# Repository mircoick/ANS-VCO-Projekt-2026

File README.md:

17.07.2026

<div align="center">

# VCO Design und Simulation

**Entwicklung und Inbetriebnahme eines Wien-Robinson-Oszillators als
Voltage-Controlled-Ozillator ($f_0=5,5~\text{MHz}$)**

<table style="border: none; border-collapse: collapse; margin: 0 auto;" border="0">

<tr style="border: none;">

<td style="border: none; padding: 0 25px; text-align: center;">

Tassilo Hertling

</td>

<td style="border: none; padding: 0 25px; text-align: center;">

Torben Becker

</td>

<td style="border: none; padding: 0 25px; text-align: center;">

Mirco Ick

</td>

</tr>

</table>

</br> </br>

**Dateiübersicht**

[KiCad-Dateien](kicad/) · [Simulationsdaten](sim/) · [Python
Code](code/) · [Datenblätter](datasheets/)

</div>

------------------------------------------------------------------------

# Einleitung

In diesem Projekt gilt es einen VCO (Voltage Controlled Oszillator) zu
designen und in Betrieb zu nehmen. Das Design soll bestimmte
Anforderungen erfüllen, damit es in einem Laborversuch als FM-Modulator
genutzt werden kann. In der Vergangenheit wurde im Laborversuch eine VCO
Schaltung mit alten und abgekündigkten Komponenten verwendet. Diese
Schaltung soll nun mit neuen und verfügbaren Komponenten erneuert
werden.

Die VCO Schaltung soll eine FM-Modulation mit einem Trägersignal bei der
Frequenz $5,5~\text{MHz}$ durchführen und einen Modulationsbereich
zwischen $5~\text{MHz}$ und $6~\text{MHz}$ verwenden. Der
Einstellungsbereich soll mit $1~\text{V}$ pro $1~\text{MHz}$ eingestellt
werden. Somit kann das zu modulierende Signal einen Spannungsbereich von
$V_{pp} = 1~\text{V}$ haben. Die Ein- und Ausgangsimpedanz soll
$50~\Omega$ betragen.

Zudem soll die Schaltung aus Komponenten bestehen, die Studierenden im
4.Semester bereits kennen, damit die Schaltung im Rahmen des
Laborversuchs im Grunde verstanden werden kann. Aus dieser
Rahmenbedingung folgt die Auswahl der spezifischen VCO-Schaltung.

Die Platine soll zudem relativ groß ausgelegt werden und es sollen
möglichst bedrahtete Bauteile verwendet werden. In dem Laborversuch soll
ebenfalls die Kennlinie des FM-Modulators aufgenommen werden. Hierfür
ist ein integrierter einstellbarer Spannungsteiler vorgesehen, der über
einen Drehregler auf der Platine eingestellt werden soll.

Die Schaltung soll ebenfalls Stabil gegenüber Schwankungen in der
Versorgungsspannung und somit in der Ausgangsfrequenz ausgelegt sein.
Anschlüsse für die im Laborversuch verwendeten Geräte wie das
Oszilloskop und dem Spektrumanalysator sollen über SMA- oder
BNC-Anschlüsse geschehen.

# Technische Spezifikationen (Kundenanforderungen)

- **Mittenfrequenz ($f_0$):** $5,5~\text{MHz}$ (Zwischenfrequenz / ZF)
  bei einer Steuerspannung von $0~\text{V}$.

- **Linearer Modulationsbereich:** $\pm 0,5~\text{MHz}$ (Frequenzhub)
  bei einer Steuerspannung von $\pm 0,5~\text{V}$.

  - *Arbeitsbereich:* $5,0~\text{MHz}$ bis $6,0~\text{MHz}$ linear im
    Spannungsbereich von $-0,5~\text{V}$ bis $+0,5~\text{V}$.

- **Frequenzstabilität:** Es darf keine Frequenzverschiebung (Drift)
  durch thermische oder externe Einflüsse auftreten.

- **Systemimpedanz:** Ein- und Ausgangswiderstand müssen exakt
  $50~\Omega$ betragen.

- **Steckverbinder:** Ein- und Ausgänge sind als **SMA-** oder
  **BNC-Buchsen** auszuführen.

- **Schaltungsarchitektur:** Einfacher, leicht zu verstehender und
  nachvollziehbarer Aufbau (diskreter Bauelemente).

- **Spannungsversorgung:** Integrierte Stabilisierung und Filterung der
  Versorgungsspannung zur Rauschunterdrückung.

- **Manuelle Steuerung:** Integrierter Spannungsteiler mit einem
  analogen Drehknopf (Potentiometer) zur Frequenzeinstellung.

- **Platinedesign:** Relativ große, robuste und mechanisch
  unempfindliche Leiterplatte.

- **Bestückungstechnologie:** Ausschließlich **stehende, bedrahtete
  Bauteile** für optimale Zugänglichkeit (keine SMD-Bauteile).

# Designverlauf

## Grundlegender VCO

Zuerst wurde im Design angefangen ein passendes VCO-Modell nach den
Anforderungen auszusuchen. Als Modell haben wurde sich für den LC-VCO
entschieden. Dieser besteht im Grunde aus einer RLC-Schaltung und einer
kreuzgekoppelten Mosfet-Schaltung. Das Design ist somit gut für
Studierende aus dem 4. Semester zu verstehen und kann auch gut mit
bedrahteten Bauteilen aufgebaut werden. Die Grundschaltung ist in
<a href="#fig-circuit" class="quarto-xref">Abbildung 1</a> zu sehen:

<div id="fig-circuit">

Abbildung 1: VCO-Grundschaltung

</div>

In der Grundschaltung sind im oberen Bereich die beiden Induktivitäten
$L1$ und $L2$ in doppelter Ausführung zu sehen, da die
Versorgungsspannung mittig angeschlossen werden muss, um die Symmetrie
der Schaltung gewärleisten zu können. Weiter unten ist der einstellbare
Kondensator $C1$ zu sehen, dessen Wert die Schwingung der Schaltung
maßgeblich beeinflusst. Durch die Änderung des Kondensator ändert sich
auch die Frequenz $f_0$ der Schaltung. Somit kann duch eine gesteuerte
Änderung der Kapazität die Frequenz der Schwingung eingestellt werden.
Das ist das Grundprinzip des VCO´s und die Funktionsweise der
FM-Modulation. Der Widerstand $R1$ vervollständigt den RLC-Schwingkreis.
Die beiden kreugekoppelten Mosfets sind für die ständige Anregung der
Schwingung zuständig. Durch die ständige Änderung der gesamt Impedanz
des Schwingkreises ändert sich jeweils der Strom, der durch die Mosfets
am Gate Eingang anliegt. Diese Änderung bewirkt eine Rückgekoppelte
Schleife, durch welche schwingt das System dauerhaft. Nach
Implementierung dieser Schaltung in KiCad, NG- sowie LT-Spice konnte die
Funktionsweise sowie das Einstellen der Frequenz $f_0$ klarer gemacht
werden.

Im Verlauf der Entwicklung wurde sich entschieden verschiede VCO Ansätze
zu entwerfen und am Ende dem Kunden zu präsentieren. Unter den drei
Gruppen konnte sich neben dem Grund-VCO, welcher oben bereits erklärt
wurde, der Colpitts Oszillator oder der Wien-Robinson-Oszillator
ausgesucht werden. Da sich bereits im zweiten Semester ausgiebig mit der
Wien-Robinson Brücke auseinander gesetzt wurde haben wir uns für diesen
VCO entschieden, auf welchen in den nachfolgenden Kapiteln näher
eingegangen wird.

Eine Simulationsdatei ist dem Ordner
[VCO-Schwingkreis](kicad/Archiv/VCO-Schwingkreis/) zu entnehmen.

## Wien-Robinson-Oszillator

Um den Wien-Robinson-Oszillator besser verstehen zu können wurde sich
als erstes die Grundschaltung, die Wien-Robinson-Brücke, nochmals
angeschaut. Hierbei handelt es sich um eine frequenzabhängige
Wechselstrom-Messbrücke, die als sogenannte Nullbrücke konzipiert ist.
Das bedeutet, dass die Differenzspannung in der Brückendiagonale bei
einer spezifischen Resonanzfrequenz exakt
$\underset{\scriptscriptstyle\sim}{U} = 0~\text{V}$ beträgt. Ein
Schaltung ist der
<a href="#fig-wienrobbruecke" class="quarto-xref">Abbildung 2</a> zu
entnehmen.

<div id="fig-wienrobbruecke">

Abbildung 2: Wien-Robinson-Brücke
(<span class="nocase">de-academic.com</span> 2000-2026)

</div>

Wenn man nun an diese Brückendiagonale einen Operationsverstärker (OPV)
einbaut, erhält man einen aktiven Oszillator, der die
Frequenzselektivität der Brücke nutzt. Da der OPV die verschwindend
geringe Differenzspannung im Bereich der Resonanzfrequenz extrem hoch
verstärkt, reicht bereits das thermische Rauschen der Bauteile aus, um
das System resonant anzuregen. Somit erhält man einen sich selber
anwingenden Oszillator. Diese Wien-Robinson-Oszillator Schaltung ist
eine der meistgenutzen Schaltungen einer Wien-Robinson-Brücke und bietet
somit eine gute Grundlage des VCO’s. Für die ersten Tests mit dem
Wien-Robinson-Oszillator wurde die Seite des Elektroniktutors
herangezogen und versucht, die entsprechende Schaltung nachzustellen
(Mietke 2002-2026).

<div id="fig-wien">

Abbildung 3: Wien-Robinson-Oszillator Schaltung (Mietke 2002-2026)

</div>

Die in <a href="#fig-wien" class="quarto-xref">Abbildung 3</a> zu
sehende Schaltung zeigt wie bereits erörtert den in der
Brückendiagonalen eingebaute Operationsverstärker und eine zusätzliche
Amplitudenregulierung. Durch die starke Anregung der Schwingung des
OPV’s wurde hier noch eine Amplitudenregelung eingebaut, welche aus
einem Potentiometer und zwei entgegengeschalteten Varktordioden besteht.
Ohne diese Amplitudenregelung würde die Schwingung aufgrund der
unendlichen Verstärkung des OPV schnell bis an die Grenzen der
Versorgungsspannung anwachsen und begrenzen, was zu starken Verzerrungen
des Sinussignals führen würde. Die Regelung sorgt dafür, dass sich ein
stabiler, verzerrungsfreier Dauerschwingzustand einstellt.

Nachdem nun diese Schaltung erfolgreich in KiCAD, erst auf der
ursprünglichen Resonanzfrequenz $f_0=1592~\text{Hz}$ und anschließend
mit Änderung des OPV’s (LT7171) auf die gewünschten $5,5~\text{MHz}$,
umgesetzt wurde, konnte sich um den geforderten Frequenzhub von
$\Delta f=1~\text{MHz}$ bei einer Steuerspannungsänderung von
$U_{str}=\pm 0,5~\text{V}$ gemacht werden. Für den ersten Entwurf wurden
nun Varaktoren parallel zu den beiden Kondensatoren $C$ geschaltet.

Nach umsetzen dieser Schaltung haben sich jedoch zwei Probleme
kristallisiert. Zum einen kamen in den verschiedenen Simulationen (KiCAD
bzw. NG-Spice und LT-Spice) unterschiede Ergebnisse heraus, und zum
anderen war es nicht möglich die Kennlinie der Resonanzfrequenz $f_0$
über die Steuerspannung $U_{str}$ linear zu bekommen. Nach vielen
vergeblichen Versuchen wurde sich dann dazu entschieden den kompletten
Aufbau neu aufzusetzen und eine andere Schaltung zu verwenden.

## Wien-Robinson VCO

Die nachfolgende Schaltung in
<a href="#fig-wien-vco" class="quarto-xref">Abbildung 4</a> ist die
verwendete Schaltung für den Wie-Brücken-VCO. Am Anfang auf der linken
Seite ist die Verstärkerschaltung für die Steuerspannung der
Varaktordioden zu sehen. Diese soll die Einstellmöglichkeit für einen
Spannungsbereich zwischen $0~\text{V}$ und $1~\text{V}$ ermöglichen.
Diese Spannung geht über einen Widerstand auf die jeweiligen Kathoden
der Varaktordioden. Diese ändern ihre Kapazität in Abhängigkeit der
Steuerspannung. Der paralelle Kondensator ist hierbei für einen Offset
der Frequenz eingebaut worden und ist Teil der Wien-Brücke. Die Wien
Brücke ist in der Mitte der Schaltung zu sehen, bestehend aus insg. vier
Varaktordioden (D2-D5), zwei Kondensatoren (C1,C2) und zwei Widerständen
(R1,R2). Die Nachfolgende Verstärkerschaltung, bestehend aus U1, R3 und
R4 ist für die Verstärkung der Schwingung und aufrechterhaltung
zuständig. Die Verstärkung ist hier mit R3 und R4 auf Faktor 3
eingestellt. Die Amplitudenregelung zum Einschwingen der Schaltung ist
auf der unteren rechten Seite zu sehen. Diese besteht aus D1, C3, R5,
R7, R8 und J1. Diese Kombination regelt die Verstärkung am Anfang des
Einschwingverhalten höher als 3, damit die Schaltung in einen sicheren
Eingeschwungenen Zustand gerät. Sobald die Amplitude den eingestellten
Wert erreicht, regelt sich die Verstärkung automatisch über J1 wieder
auf 3 runter. Die Schaltung schwingt nun stabil.

<div id="fig-wien-vco">

Abbildung 4: Wien-Robinson-Oszillator VCO Schaltung (Geißler u. a. 1993)

</div>

Wir haben uns speziell für diese Schaltungsart entscheiden, da die
steuerbare Amplitudenregelung anfangs bessere Ergebnisse in der
Simulation mit NGSpice und LTSpice bezüglich der linearität der
Ausgangsfrequenz bessere Ergebnisse lieferte.

## Komponenten

Um den Wien-Robinson-Oszilator im gewünschten Frequenzbereich schwingen
zu lassen, musste die Grundschaltung angepasst werden und um
entsprechende Bauteile ersetzt werden.

### Operationsverstärker

Da die Schaltung maximal bei $6~\text{MHz}$ schwingen soll muss der OPV
sowohl ultra-high-speed sein als auch eine hohe Slew-rate haben.

### Varaktordioden

Damit die Mittenfrequenz verschoben werden kann, wurden varaktoren
Parrallel zu den Kondensatoren der Wien-Robinson-Brücke geschaltet. Um
sich in einem Lineraren Berreich zu bewegen müssen die Kennlinien der
Varaktoren in dem beschalteten Berreich auch linerar sein. Zudem müssen
diese eine möglichst hohe Änderung der Kapazität in diesem Berreich
vorweisen.

### Diode

Die Diode in der rückführenden Verstärkerschaltung des VCO´s muss
ebenfalls eine sehr schnelle Schottkydiode sein, da sie ebenfalls die
Signale von maximal $6~\text{MHz}$ sperren und durchlassen soll.

### Transistor

Der Transistor muss in diesem Fall ein J-FET, also ein Transistor,
welcher ohne Spannung maxiaml Leitend ist, eingebaut werden. Dieser wird
mit einer negativen Gleichspannung versorgt und muss somit nicht
High-Speed sein.

# Charakterisierung

Nachdem nun der Aufbau und die meisten Bauteile feststanden konnte sich
mit Hilfe von LTSpice eine Simulation des Aufbaus zusammengestellt
werden. Die Simulationsdateien können dem Ordner [sim](sim/) entnommen
werden.

## Bauteilauswahl der Varaktor-Diode

Die bereitgestellte [Varaktor-Dioden-Bibliothek](kicad\spicelibs)
umfasst 30 Einzelmodelle. Um eine Diode zu identifizieren, die eine
nahezu lineare Kapazitätsänderung von $\Delta C \approx 14~\text{pF}$
über einen Steuerspannungsbereich von $V_{str} = 3~\text{V}$ aufweist,
wurde ein Capometer eingesetzt. Dieses Capometer ermöglichte die
automatisierte Auswertung der Kennlinien, um die optimale Komponente für
die geplante Schaltung festzulegen. Es wird hier bei einer linear
ansteigenden Spannung die Kapazität der Diode in einer $C(V)$-Kennline
aufgetragen, wodurch der benötigte Kapaziätsunterschied direkt abgelesen
werden kann. Die LTSpice Schematic ist [hier](sim/capometer.asc)
zufinden.

Die Analyse der Modelle ergab, dass die
[BB535/SIE](datasheets/BB535.pdf) Varaktor Diode am besten zu den
Anforderungen passt. Somit wurden alle benötigten Bauteile gefunden und
die Silumation konnte durchgeführt werden.

## Simulation den Wien-Brücken-VCO’s

Um nun die Schaltung Simulieren zu können wurde LTSpice sowie auch
NGSpice über KiCAD zur Hilfe genommen. In beiden Fällen konnte der in
<a href="#fig-wien-vco" class="quarto-xref">Abbildung 4</a> zu sehende
Schaltungsaufbau genommen werden und mit den passenden Werten sowie
Bauteilen verknüpft werden. Das Simulationsergebnis der Schaltung
([KiCAD](kicad/Wien-VCO/)) Ausgewertet mit dem
[sim_plot.py](code/sim_plot.py) Skript ist der
<a href="#fig-sim-wien-vco" class="quarto-xref">Abbildung 5</a> zu
entnehmen. Für die LTSpice sowie NGSpice Bauteile wurden folgende Werte
festgelegt:

<div class="columns" style="display: flex; align-items: center;">

<div class="column" width="45%">

| Symbol | Bauteil | Typ / Wert | Model |
|:--------|:--------|:--------|:--------|
| **U1**      | Operationsverstärker | MAX4104 |[MAX4104.lib](kicad/spicelibs/) |
| **U2**      | Operationsverstärker | TL082 |  [elk.lib](kicad/spicelibs/) |
| **J1**      | JFET | J113 |                   [J113.lib](kicad/spicelibs/) |
| **D1**      | Diode | 1N6263 (Schottky) |   [.model 1N6263](kicad/spicelibs/models.txt)   |
| **D2-D5**   | Kapazitätsdiode |  BB535/SIE  |  [.model BB535](kicad/spicelibs/models.txt)  |
| **C1-C2**   | WRB Kondensator | $2{,}7~\text{pF}$   | |
| **C3**      | Regelungs Kondensator | $2{,}0~\text{nF}$   | |
| **C4-C5**   |$V_{str}$ Kondensator | $100~\text{nF}$     | |
| **R1-R2**   | WRB Widerstand | $3{,}275~\text{k}\Omega$ | |
| **R3**      | Verstärker Widerstand | $2{,}32~\text{k}\Omega$  | |
| **R4**      | Verstärker Widerstand | $1{,}2~\text{k}\Omega$   | |
| **R5**      | Regelungs Widerstand | $20~\text{k}\Omega$      | |
| **R6, R9**  | $V_{str}$ Widerstand | $100~\text{k}\Omega$     | |
| **R7**      | Regelungs Widerstand | $1{,}0~\text{k}\Omega$   | |
| **R8**      | Regelungs Widerstand | $8{,}0~\text{k}\Omega$   | |
| **R10**     | $V_{str}$ Widerstand | $10~\text{k}\Omega$      | |
| **R11**     | $V_{str}$ Widerstand | $75~\text{k}\Omega$      | |
| **R12**     | $V_{str}$ Widerstand | $50~\text{k}\Omega$      | |

</div>

</div>

<div id="fig-sim-wien-vco">

Abbildung 5: Simulationsergebnis mit Python Auswertung

</div>

Die in <a href="#fig-sim-wien-vco" class="quarto-xref">Abbildung 5</a>
dargestellte Simulation zeigt die vollständige Schaltung im
einstellbaren Steuerspannungsbereich von $V_{str} = 0 \dots 1~\text{V}$.
Die Auswertung umfasst drei Darstellungen:

Der obere Plot zeigt die Zeitsignale der 11 simulierten Zustände.
Hierbei lässt sich die Amplitudenstabilität der Schaltung überprüfen. Zu
sehen ist, dass die Amplitude über den gesamten Steuerspannungsbereich
sowohl im positiven als auch im negativen Bereich bei ca.
$\pm 9~\text{V}$ stabil bleibt. Die unterschiedlichen Frequenzen der
Signale sind bereits im Zeitbereich visuell erkennbar.

Um nun die Frequenzanteile genauer zu betrachten dient der untere linke
Plot, welcher die Fast Fourier Transformation (FFT) der Signale
visualisiert. Die Darstellung ermöglicht den Abgleich mit den
Kundenvorgaben für die Mittenfrequenz ($f_0 = 5,5~\text{MHz}$) sowie den
Grenzfrequenzen ($f_u = 5~\text{MHz}$ bis $f_o = 6~\text{MHz}$). Die
Analyse zeigt, dass bei einer Steuerspannung von $V_{str} = 0~\text{V}$
nahezu exakt $5~\text{MHz}$ erreicht werden. Die obere Grenzfrequenz
wird mit ca. $6,025~\text{MHz}$ nur minimal überschritten, was für eine
sehr gute Abstimmung der Schaltung spricht.

Der dritte Plot implimentiert die berechneten Peak-Frequenzen der FFT
mit der Steuerspannung. Im Idealfall entspräche die Kennlinie einer
Geraden, die exakt bei $(0~\text{V}, 5~\text{MHz})$ beginnt und bei
$(1~\text{V}, 6~\text{MHz})$ endet. Die Simulationsergebnisse bilden
diesen Verlauf sehr präzise ab. Die geringfügigen Abweichungen sind
primär auf die in LTspice bzw. NGspice hinterlegten Bauteiltoleranzen
sowie auf physikalisch notwendige Kompromisse bei der Bauteilwahl
zurückzuführen.

Zusammenfassend liegen die Simulationsergebnisse über den Erwartungen
und zeigen die Funktionalität sowie die gute Machbarkeit der zu
entwerfenden Wien-Brücken-VCO Platine.

## Fertige Platine

Im folgenden ist der Messaufbau zur Messwertaufnahme und
Charakterisierung der Schaltung zu sehen. Für die Spannungsversorgung
beider Operationsverstärker wurde enine Spannungsquelle verwendet,
welche auf $5~\text{V}$ eingestellt wurde. Die Spannung und somit die
Frequenz wurde mit einem PicoScope Oszilloskop aufgenommen.

<div id="fig-plat1">

Abbildung 6: Platine 1

</div>

Die beiden weiteren Bilder zeigen die bestückte Platine. Diese umfasst
die Wie-Robinson-Brücke mit den Varaktoren und der Verstärkerschaltung
des Oszillatorteils mit Ampltitudenregelung. Die Verstärkerschaltung der
Steuerspannung wurde auf dem Breadboard aufgebaut.

Die Platine wurde mit der, sich im kicad Ordner befindlichen
PDF-Dateien, belichtet und anschließend geätzt. Im Anschluss wurden alle
Löcher gebohrt und die Platine bestückt.

Aufgrund von parasitären Eigenschaften des Messaufbaus sowie des Platinenlayouts wichen die im realen Aufbau verwendeten Bauteilwerte von den ursprünglichen Simulationswerten ab. Diese Anpassungen waren notwendig, um die gewünschten Zielvorgaben und Spezifikationen zu erreichen. Die betroffenen Komponenten und ihre angepassten Werte sind in der folgenden Tabelle zusammengefasst:

<div class="columns" style="display: flex; align-items: center;">

<div class="column" width="45%">

| Symbol | Bauteil | Typ / Wert |
|:--------|:--------|:--------|
| **C3**      | Regelungs Kondensator | $1{,}0~\text{nF}$   |
| **R1-R2**   | WRB Widerstand | $3{,}275~\text{k}\Omega$ |
| **R3**      | Verstärker Widerstand | $2{,}32~\text{k}\Omega$  |
| **R4**      | Verstärker Widerstand | $1{,}2~\text{k}\Omega$   |
| **R5**      | Regelungs Widerstand | $20~\text{k}\Omega$      |
| **R6, R9**  | $V_{str}$ Widerstand | $100~\text{k}\Omega$     |
| **R7**      | Regelungs Widerstand | $1{,}0~\text{k}\Omega$   |
| **R8**      | Regelungs Widerstand | $8{,}0~\text{k}\Omega$   |
| **R10**     | $V_{str}$ Widerstand | $10~\text{k}\Omega$      |
| **R11**     | $V_{str}$ Widerstand | $75~\text{k}\Omega$      |
| **R12**     | $V_{str}$ Widerstand | $50~\text{k}\Omega$      |

<div class="columns" style="display: flex; align-items: center;">

<div class="column" width="45%">

</div>

</div>

### Messergenisse

Im folgenden sind die Messergebnisse des zuvor gezeigten Messaufbaus zu
sehen.

<div id="fig-test">

Abbildung 7: Darstellung der Messergebnisse mit Python

</div>

Das obere Diagramm zeigt die Spannung am Ausgang des VCOs. Diese bleibt
ebenfalls über den gesamten Steuerbereich konstant bei einer Amplitude
von etwa $\pm 35~\text{mV}$. Zudem ist eine leichte Verzerrung der
Schwingung zu erkennen, dies ist auf den Operationsverstärker und deren
Amplitudensteuerung zurückzuführen. Anhand des Spektrums sind ebenfalls
die Peaks im Bereich des benötigten Frequenzbereichs zu sehen. Diese
ordnen sich präzise zwischen den markierten Grenzfrequenzen von
$5,0~\text{MHz}$ und $6,0~\text{MHz}$ ein, wobei sich das Nutzsignal
bei etwa $-30~\text{dBV}$ mit einem hohen Störabstand deutlich vom
Grundrauschen abhebt. Die Kennlinie der Steuerspannung zu der
Ausgangsfrequenz zeigt ebenfalls ein deutliches lineares Verhalten, wie
bereits in der Simulation zu sehen. Der abgebildete Steuerbereich von
$0~\text{V}$ bis $1~\text{V}$ deckt den geforderten Frequenzhub
präzise ab, wobei die Kurve bei $0~\text{V}$ exakt bei
$5,0~\text{MHz}$ startet und bei $1~\text{V}$ den oberen Grenzwert von
$6,0~\text{MHz}$ erreicht

# Ordnerstruktur

``` {text}
.
├── code/
├── data/
├── datasheets/
├── images/
├── kicad/
│   ├── Archiv/
|       ├── VCO-Schwingkreis/
│   ├── footprints/
│   ├── spicelibs/
│   └── Wien-VCO/
├── report/
├── sim/
├── .gitignore
└── README.md
```

# Literaturverzeichnis

<div id="refs" class="references csl-bib-body hanging-indent">

<div id="ref-wienrobinsonbruecke" class="csl-entry">

<span class="nocase">de-academic.com</span>. 2000-2026.
*Wien-Robinson-Brücke*. Design Reference.
<https://de-academic.com/dic.nsf/dewiki/1507065>.

</div>

<div id="ref-geissler1993" class="csl-entry">

Geißler, Rainer, Werner Kammerloher, und Hans Werner Schneider. 1993.
*Berechnungs- und Entwurfsverfahren der Hochfrequenztechnik 1*.
Vieweg+Teubner Verlag Wiesbaden.
<https://doi.org/10.1007/978-3-322-84915-1>.

</div>

<div id="ref-wienbruecke" class="csl-entry">

Mietke, Detlef. 2002-2026. *Wien-Robinson-Oszillator*. Design Reference.
<https://www.elektroniktutor.de/signalkunde/wien_osz.html>.

</div>

</div>

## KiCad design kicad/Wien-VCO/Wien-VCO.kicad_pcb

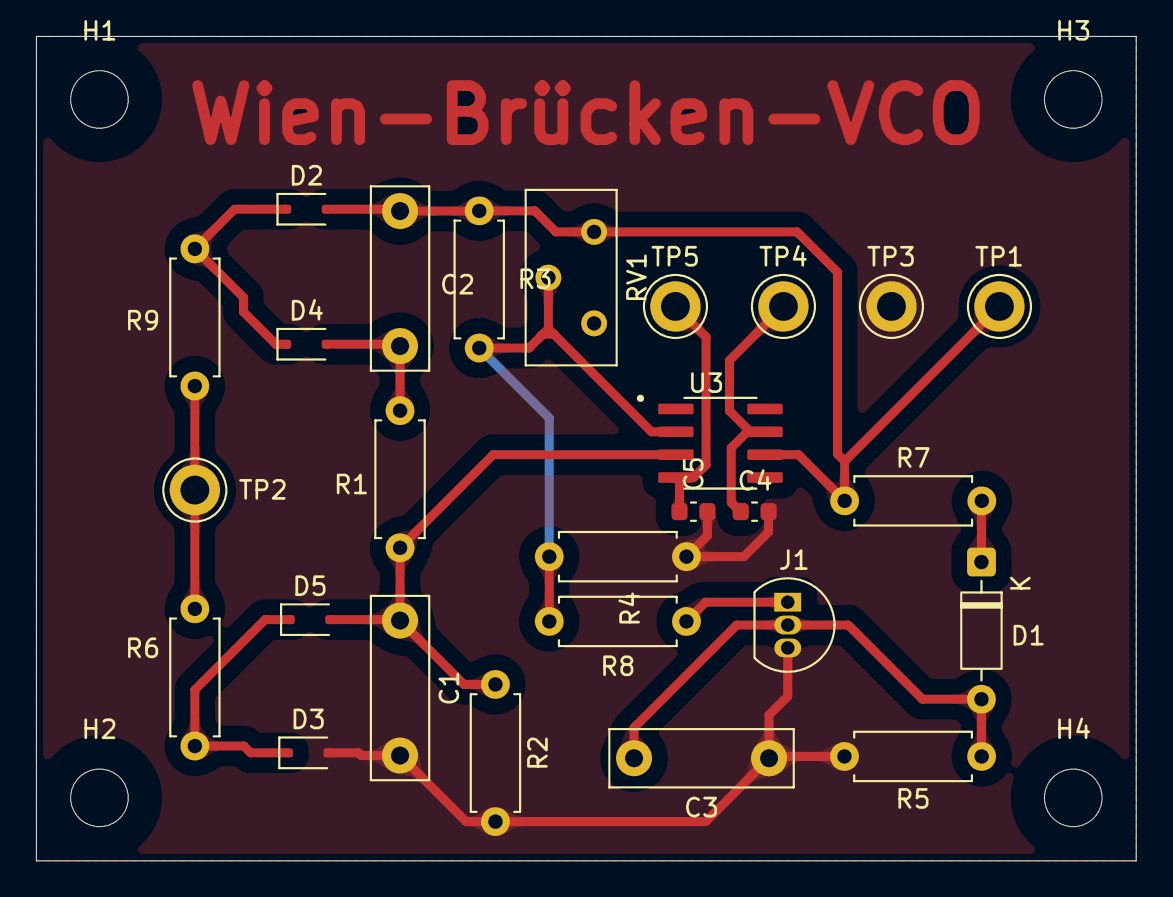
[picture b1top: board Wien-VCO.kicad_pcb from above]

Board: 2 copper layers, 61.1 x 45.8 mm, 31 parts (0 on the bottom side), 14 nets.

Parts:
C1, C2: {C}; C_Rect_L10.0mm_W3.0mm_P7.50mm_MKS4
C3: 2nF; C_Rect_L10.0mm_W3.0mm_P7.50mm_MKS4
C4, C5: 100nF; C_0603_1608Metric
D1: 1N6263; D_DO-35_SOD27_P7.62mm_Horizontal
D2, D3, D4, D5: BB535/SIE; D_SOD-323F
H1, H2, H3, H4: MountingHole; MountingHole_3.2mm_M3_ISO7380
J1: J113; TO-92_Inline
R1, R2: {R}; R_Axial_DIN0207_L6.3mm_D2.5mm_P7.62mm_Horizontal
R3: 2K23; R_Axial_DIN0207_L6.3mm_D2.5mm_P7.62mm_Horizontal
R4: 1K2; R_Axial_DIN0207_L6.3mm_D2.5mm_P7.62mm_Horizontal
R5: 20K; R_Axial_DIN0207_L6.3mm_D2.5mm_P7.62mm_Horizontal
R6, R9: 100K; R_Axial_DIN0207_L6.3mm_D2.5mm_P7.62mm_Horizontal
R7: 1K; R_Axial_DIN0207_L6.3mm_D2.5mm_P7.62mm_Horizontal
R8: 8K; R_Axial_DIN0207_L6.3mm_D2.5mm_P7.62mm_Horizontal
RV1: R_Potentiometer; Potentiometer_Bourns_3296Y_Vertical
TP1, TP2, TP3, TP4, TP5: TestPoint; TestPoint_Keystone_5010-5014_Multipurpose
U3: MAX4104ESA_; SOIC127P600X175-8N_neu

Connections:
0: C1.2, C3.1, C4.1, C5.1, D3.2 (A), J1.3 (S), R2.2, R4.2, R5.2, TP3.1 (1_1)
unnamed: C3.2, D1.2 (A), J1.2 (G), R5.1
unnamed: D1.1 (K), R7.2
unnamed: D2.1 (K), D4.1 (K), R9.2
unnamed: D3.1 (K), D5.1 (K), R6.2
unnamed: C2.2, D4.2 (A), R1.1
unnamed: J1.1 (D), R8.2
unnamed: U3.1 (NC), U3.5 (NC), U3.8 (NC)
V2: C1.1, D5.2 (A), R1.2, R2.1, U3.3 (IN+)
VCC+: C4.2, TP4.1 (1_1), U3.7 (VCC)
VCC-: C5.2, TP5.1 (1_1), U3.4 (VEE)
Va: C2.1, D2.2 (A), R3.2, R7.1, RV1.3, TP1.1 (1_1), U3.6 (OUT)
Ve: R3.1, R4.1, R8.1, RV1.2, U3.2 (IN-)
Vstr: R6.1, R9.1, TP2.1 (1_1)

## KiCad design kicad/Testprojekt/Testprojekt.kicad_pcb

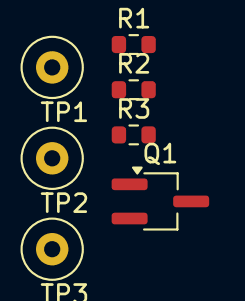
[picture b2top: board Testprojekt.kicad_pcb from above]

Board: 2 copper layers, 7 parts (0 on the bottom side), 4 nets, no tracks yet.

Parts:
Q1: NMOS; TSOT-23_HandSoldering
R1: 75K; R_0603_1608Metric
R2: 39K; R_0603_1608Metric
R3: 600R; R_0603_1608Metric
TP1, TP2, TP3: TestPoint; TestPoint_Loop_D2.60mm_Drill0.9mm_Beaded

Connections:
/VDD: R1.1, TP2.1 (1_1)
/VG: Q1.2 (G), R3.2, TP1.1 (1_1)
/vd: Q1.1 (D), R1.2
GND: Q1.3 (S), R2.2, TP3.1 (1_1)

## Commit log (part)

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2026-04-16 Kundenanforderungen
2026-04-16 Added report and kicad fm-vco
2026-04-16 Added gitignore
2026-04-16 KiCAD Projekt
2026-04-16 Added elk spicelib
2026-04-16 Cleaned pdf file and backup dir
2026-04-17 Dokumentation
2026-04-23 Update Kundenanforderungen
2026-04-23 Testprojekt Update
2026-04-23 haaaaaa
2026-04-23 read_raw
2026-04-23 read_raw2
2026-05-07 Ordner Code für Python Auswertung hinzugefügt
2026-05-07 Aufräumen
2026-05-07 Aufräumen die Zweite
2026-05-07 KiCad VCO-Schwingkreis Projekt Aktualisierung
2026-05-08 Anfang der Dokumentation
2026-05-08 Reorder
2026-05-08 Cleared reporting
2026-05-11 Schwingkreis mit 5,5MHz
2026-05-16 Update des Reports
2026-05-20 Plot Update
2026-05-20 Ordnung geschaffen
2026-05-20 Update Plot 2.0 / VCO Werte gefunden
2026-05-21 Kapazitätsdiode eingebaut
2026-05-21 Wien-Brücken-Oszillator hinzugefügt
2026-05-21 Wien-Brücken-Schwinger mit JFET zur Amplitudenstabilisierung
2026-06-04 Wien-Brpcken-Schwinger-Dioden hinzugefügt
2026-06-04 Spice Libs LT7171 hinzugefügt
2026-06-10 5.5 MHz Update
2026-06-10 Archiv erstellt
2026-06-10 Pfade angepasst
2026-06-11 Python Skript
2026-06-11 Update 5.5 MHz
2026-06-11 LTSpice Simulation
2026-06-11 Debugged LTSpice
2026-06-11 Erste Änderungen, Abgleiche LTspice vs ngspice
2026-06-12 Schaltung in LTSpice angepasst
2026-06-12 LTSpice schaltung update
2026-06-16 KiCAD und LTspice Modell MM
2026-06-16 Review Auswertung Py
2026-06-18 Added capometer for varactor diodes
2026-06-18 Varaktoren Änderung auf Linearität
2026-06-18 FT-Wien
2026-06-18 capometer
2026-06-18 DAtasheet
2026-06-23 Neue Varaktoren
2026-06-25 Schaltung mit neuen Bauteilen
2026-06-25 fix: Anpassung des .include Befehls
2026-06-25 Report Ansatz
2026-06-25 Report Wienbrücke
2026-06-25 doku
2026-06-25 Report WienOszi
2026-06-26 Added BOM_Wien-LT
2026-06-29 BOM angepasst
2026-06-29 Änderung auf neuen Varaktor
